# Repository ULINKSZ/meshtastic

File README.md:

# Meshtastic Product Development
Meshtastic devices can help explorers stay connected, share locations, send emergency distress signals, etc. in remote mountainous areas without mobile phone signals during outdoor activities such as hiking and mountaineering. In some small communities or remote villages, Meshtastic mesh networks can be built to meet local communication needs, such as community notifications and emergency warnings. In the event that natural disasters (such as earthquakes and floods) damage traditional communication infrastructure, Meshtastic devices can be quickly deployed to establish emergency communication networks to provide communication means for rescue workers and disaster victims.
=======
## Open source code link (https://github.com/meshtastic/meshtastic)
## The following are all the contents in this warehouse organized into separate directories. Each directory stores the corresponding information. When you need it, go to the specified directory to search. The name of each directory is shown below:
### Docs is the product hardware specification and hardware parameters
### Firmware is used to store the hex and bin files burned into the hardware
### Hardware/meshtastiv_V1.0 is the product schematic and PCB board. Please use Kicad software to open and view it. Kicad download address (https://www.kicad.org/)
### Instructions are product burning and usage methods and how to quickly locate. Please open the folder and click Meshtastic devices or How to quickly locate files to view them.
### Software/firmware-master is the product source code. Please download VSCode to open and view it. VsCode download address (https://code.visualstudio.com/)

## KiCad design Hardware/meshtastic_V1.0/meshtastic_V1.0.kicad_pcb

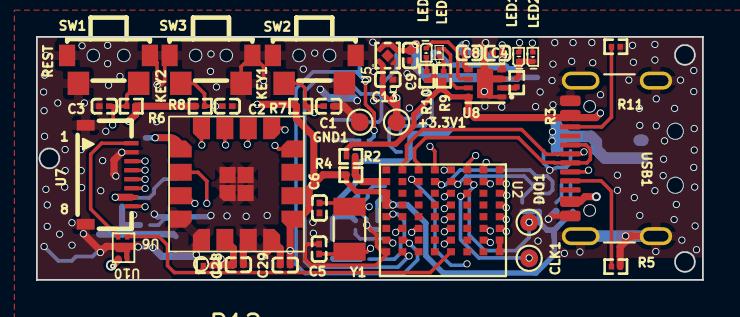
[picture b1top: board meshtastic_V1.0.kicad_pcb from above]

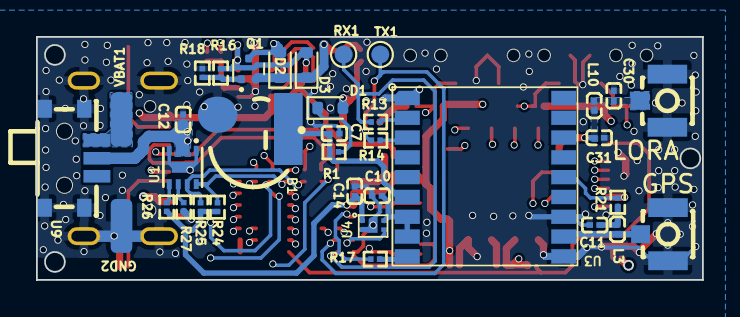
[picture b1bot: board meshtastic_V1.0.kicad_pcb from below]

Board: 4 copper layers, 37.0 x 13.5 mm, 76 parts (35 on the bottom side), 60 nets.

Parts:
+3.3V1: TEXT; TestPoint_Pad_D1.0mm
B1: XH414H-IV01E 3.3V0.08F; CAP-SMD_2P-L4.8-W4.8-TR
C1, C2, C3, C10, C28, C29: 100nF; C0201
C4, C7, C8, C12: 1uF; C0201
C5, C6: 12pF; C0201
C9, C13, C14: 105; C0201
C11: 10nF; C0201
C30, C31: 3.3pF; C0201
CLK1: TEXT; TestPoint_Pad_D1.0mm
D1, D2, D3: LRB521S-40T1G; D_SOD-523
DIO1: TEXT; TestPoint_Pad_D1.0mm
GND1: TEXT; TestPoint_Pad_D1.0mm
GND2: GND; 1P_TEST
L3: 2.66R VHF060303H68NJT; L0201
L10: 9.1nH; L0201
LED1: XL-0201UGC; LED-SMD_L0.7-W0.4-RD_GREEN
LED2: XL-0201UBC; LED-SMD_L0.7-W0.4-RD_BLUE
LED5: XL-0201SURC; LED-SMD_L0.65-W0.35-P0.41_XL-0201SURC
LED6: XL-0201UGC/NC; LED-SMD_L0.7-W0.4-RD_GREEN
Q1: CJ3139K; SOT-723
R1: 3.3K; R0201
R2: 0R; R0201
R3: 9K; R0201
R4: 0R/NC; R0201
R5, R11: 499R; R0201
R6, R7, R8, R12, R18, R27: 10K; R0201
R9: 1K; R0201
R10: 1K/NC; R0201
R13, R14, R17: 33; R0201
R16: 100R; R0201
R21: 10R; R0201
R24, R25, R26: 4.7K; R0201
RF1, RF2: IPEX(1代); IPEX
RX1: TEXT; TestPoint_Pad_D1.0mm
SW1, SW2, SW3: TS24CA; SW-SMD_TS24CA
TX1: TEXT; TestPoint_Pad_D1.0mm
U1: MAX17048G+T10; DFN-8-2x2-P0.5
U2: UL840; UL-840
U3: MAX-M10S-00B-01; MAX-M10S
U4, U10: DIO7330B; DFN-4
U5: RT9073A-33GQZ
U6: HJ-68LR(12); UL62
U7: AFC42-S08FMA-1H; FFC-SMD_8P-P0.50_AFC42-S08FMA-1H
U8: LGS4056HDA; DFN-8_L2.0-W2.0-P0.50-BL-EP
U9: MINI_MSK12CO2; SW-SMD_MSK12CO2
USB1: type-16pin; USB_C_Receptacle_GCT_USB4105-xx-A_16P_TopMnt_Horizontal
VBAT1: BAT; 1P_TEST
Y1: 32.768kHz; Crystal_SMD_3215-2Pin_3.2x1.5mm

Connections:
+3.3V: +3.3V1.1, C13.1, C14.2, C28.1, C29.2, D1.2 (A), R4.2, R6.2, R7.2, R8.2, R12.1, R24.1, R25.1, R26.1, U2.H3 (VDD), U2.H4 (VDD), U4.1 (VIN), U5.1 (VOUT), U6.2 (VCC), U6.5 (VCC), U7.7 (VDD), U10.1 (VIN)
+BATT: C8.1, C12.1, D2.2 (A), Q1.3 (D), U1.2 (CELL), U1.3 (VDD), U8.5 (BAT), U9.2
/BACKUP: B1.1, C7.1, R1.2, U3.6 (V_BCKP)
/D+: U2.F1 (D+), USB1.A6 (DP1), USB1.B6 (DP2)
/D-: U2.G1 (D-), USB1.A7 (DN1), USB1.B7 (DN2)
/GPS-EN: U2.H7 (P0.04), U4.3 (EN)
/Max_RESET: R17.2, U2.H5 (P0.08)
/RADIO_BUSY: U2.C1 (P0.25), U6.9 (BUSY)
/RADIO_DIO_1: U2.D1 (P0.19), U6.8 (DIO1)
/RADIO_RESET: U2.B1 (P0.22), U6.10 (RST)
/RESET: C3.1, R6.1, SW1.4, U2.E1 (P0.18/RESET)
/RF_ANT: C31.1, L10.1, U6.13 (ANT)
/RX: R13.2, RX1.1, U2.G8 (P0.06)
/SCL: R25.2, U1.7 (SCL), U2.E2 (P0.15)
/SDA: R24.2, U1.8 (SDA), U2.D2 (P1.00)
/SPI_MISO: U2.B2 (P1.04), U6.11 (MISO)
/SPI_MOSI: U2.A4 (P0.20), U6.14 (MOSI)
/SPI_NSS: U2.A3 (P0.21), U6.15 (NSS)
/SPI_SCLK: U2.A2 (P1.01), U6.12 (SCK)
/SWCLK: CLK1.1, U2.C3 (SWCLK)
/SWDI0: DIO1.1, U2.C2 (SWDIO)
/TX: R14.2, TX1.1, U2.G7 (P0.26)
GND: B1.2, C1.1, C2.1, C3.2, C4.2, C5.2, C6.2, C7.2, C8.2, C9.2, C10.2, C11.2, C12.2, C13.2, C14.1, C28.2, C29.1, C30.2, C31.2, GND1.1, GND2.1, LED1.1 (K), LED2.1 (K), R3.1, R5.1, R11.1, R18.1, R27.2, RF1.2 (GND), RF1.3 (GND), RF2.2 (GND), RF2.3 (GND), SW1.1, SW1.2, SW1.3, SW2.1, SW2.2, SW2.4, SW3.1, SW3.2, SW3.4, U1.1 (CTG), U1.4 (GND), U1.9 (EP), U2.A1 (GND), U2.H8 (GND), U3.1 (GND), U3.10 (GND), U3.12 (GND), U4.2 (GND), U4.5 (GND), U5.2 (GND), U5.5 (GND), U6.1 (GND), U6.3 (GND), U6.4 (GND), U6.16 (GND), U6.17 (GND), U7.2 (GND), U7.9 (GND), U7.10 (GND), U8.1 (TEMP), U8.3 (GND), U8.9 (PAD), U9.4, U9.5, U10.2 (GND), U10.5 (GND), USB1.A1 (GND), USB1.A12 (GND), USB1.B1 (GND), USB1.B12 (GND), USB1.S1 (SHELL)
KEY1: C1.2, R7.1, SW2.3, U2.A5 (P0.17)
KEY2: C2.2, R8.1, SW3.3, U2.A6 (P0.14)
LCD_CS: U2.D7 (P1.13), U7.8 (CS)
LCD_DC: U2.D4 (P1.03), U7.4 (D/C)
LCD_REST: U2.D3 (P1.02), U7.3 (RESET)
LCD_SCL: U2.D6 (P1.10), U7.6 (SCL)
LCD_SDA: U2.D5 (P0.23), U7.5 (SDA)
LEDA: U7.1 (LEDA), U10.4 (VOUT)
LEDK: R12.2, U2.D8 (P0.31), U10.3 (EN)
LED_GREEM: LED2.2 (A), U2.B7 (P1.06)
LED_RED: LED1.2 (A), U2.B6 (P0.24)
unnamed: C11.1, L3.1, R21.1
unnamed: D1.1 (K), R1.1
unnamed: LED5.1 (A), R9.1
unnamed: LED5.2 (K), U8.7 (CHRG)
unnamed: LED6.2 (A), R10.1
unnamed: LED6.1 (K), U8.6 (DONE)
unnamed: Q1.1 (G), R16.2, R18.2
unnamed: L3.2, RF1.1 (SIG), U3.11 (RF_IN)
unnamed: C30.1, L10.2, RF2.1 (SIG)
unnamed: R26.2, U1.5 (ALRT#)
unnamed: R27.1, U1.6 (QSTRT)
unnamed: U2.A7 (ANT), U2.A8 (BOARD_ANT)
unnamed: C6.1, U2.F6 (P0.00), Y1.2
unnamed: C5.1, U2.G6 (P0.01), Y1.1
unnamed: R2.1, R4.1, U2.H2 (VDDH)
unnamed: R17.1, U3.9 (RESET_N)
unnamed: R14.1, U3.3 (RXD)
unnamed: R13.1, U3.2 (TXD)
unnamed: C10.1, U3.7 (V_IO), U3.8 (VCC), U4.4 (VOUT)
unnamed: R21.2, U3.14 (VCC_RF)
unnamed: R3.2, U8.2 (PROG)
unnamed: R5.2, USB1.A5 (CC1)
unnamed: R11.2, USB1.B5 (CC2)
VAA: U9.1, VBAT1.1
VBUS: C4.1, D3.2 (A), R2.2, R9.2, R10.2, R16.1, U2.F2 (VBUS), U8.4 (VCC), U8.8 (CE), USB1.A4 (VBUS), USB1.A9 (VBUS), USB1.B4 (VBUS), USB1.B9 (VBUS)
VCC: C9.1, D2.1 (K), D3.1 (K), Q1.2 (S), U5.3 (EN), U5.4 (VIN)

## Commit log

2024-10-01 提交文件
2024-10-01 Create LICENSE
2024-10-12 Quick positioning
2024-10-15 Version update
2024-10-15 update firmware
    Resolve the screen flickering bug
2024-10-26 Fixed compilation errors
    bmaSensor.setReampAxes(bmaSensor.REMAP_BOTTOM_LAYER_BOTTOM_LEFT_CORNER); Change to bmaSensor.MAPsetRemapAxes(bmaSensor.REMAP_BOTTOM_LAYER_BOTTOM_LEFT_CORNER)
